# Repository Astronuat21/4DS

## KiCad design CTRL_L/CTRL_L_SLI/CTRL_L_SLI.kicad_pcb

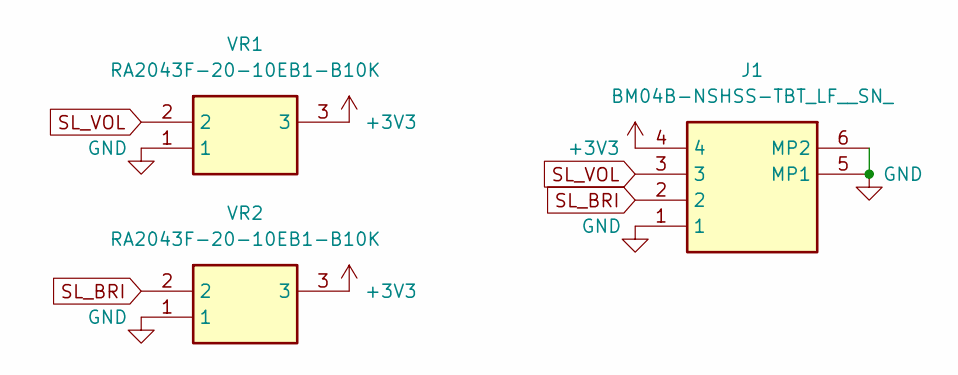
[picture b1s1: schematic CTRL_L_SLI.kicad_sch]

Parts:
J1: BM04B-NSHSS-TBT_LF__SN_; BM04BNSHSSTBTLFSN; Mouser Part Number 306-4BNSHSSTBTL
VR1, VR2: RA2043F-20-10EB1-B10K; RA2043F2010EB1B10K; Mouser Part Number 312-219BF-10K

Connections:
+3V3: J1.4, VR1.3, VR2.3
GND: J1.1, J1.5 (MP1), J1.6 (MP2), VR1.1, VR2.1
SL_BRI: J1.2, VR2.2
SL_VOL: J1.3, VR1.2

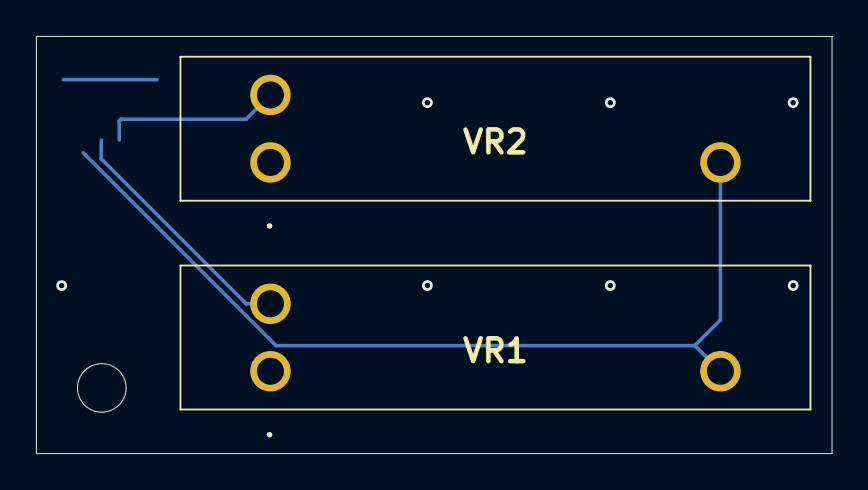
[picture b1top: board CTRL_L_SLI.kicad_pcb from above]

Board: 2 copper layers, 44.2 x 23.2 mm, 3 parts (1 on the bottom side), 4 nets.

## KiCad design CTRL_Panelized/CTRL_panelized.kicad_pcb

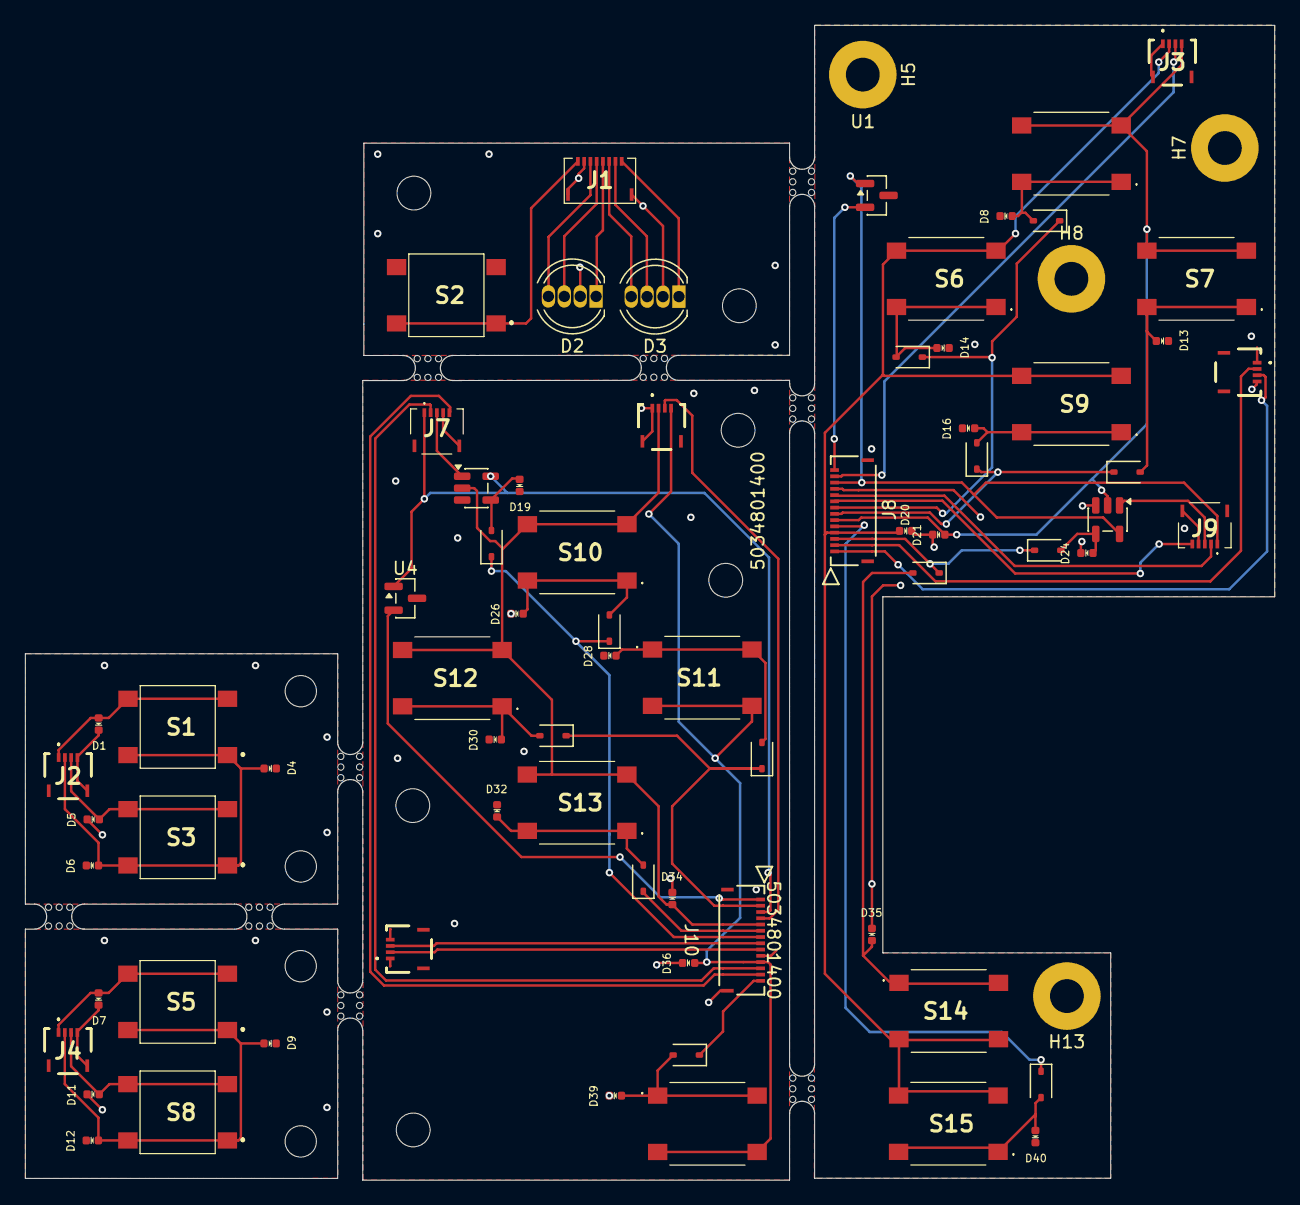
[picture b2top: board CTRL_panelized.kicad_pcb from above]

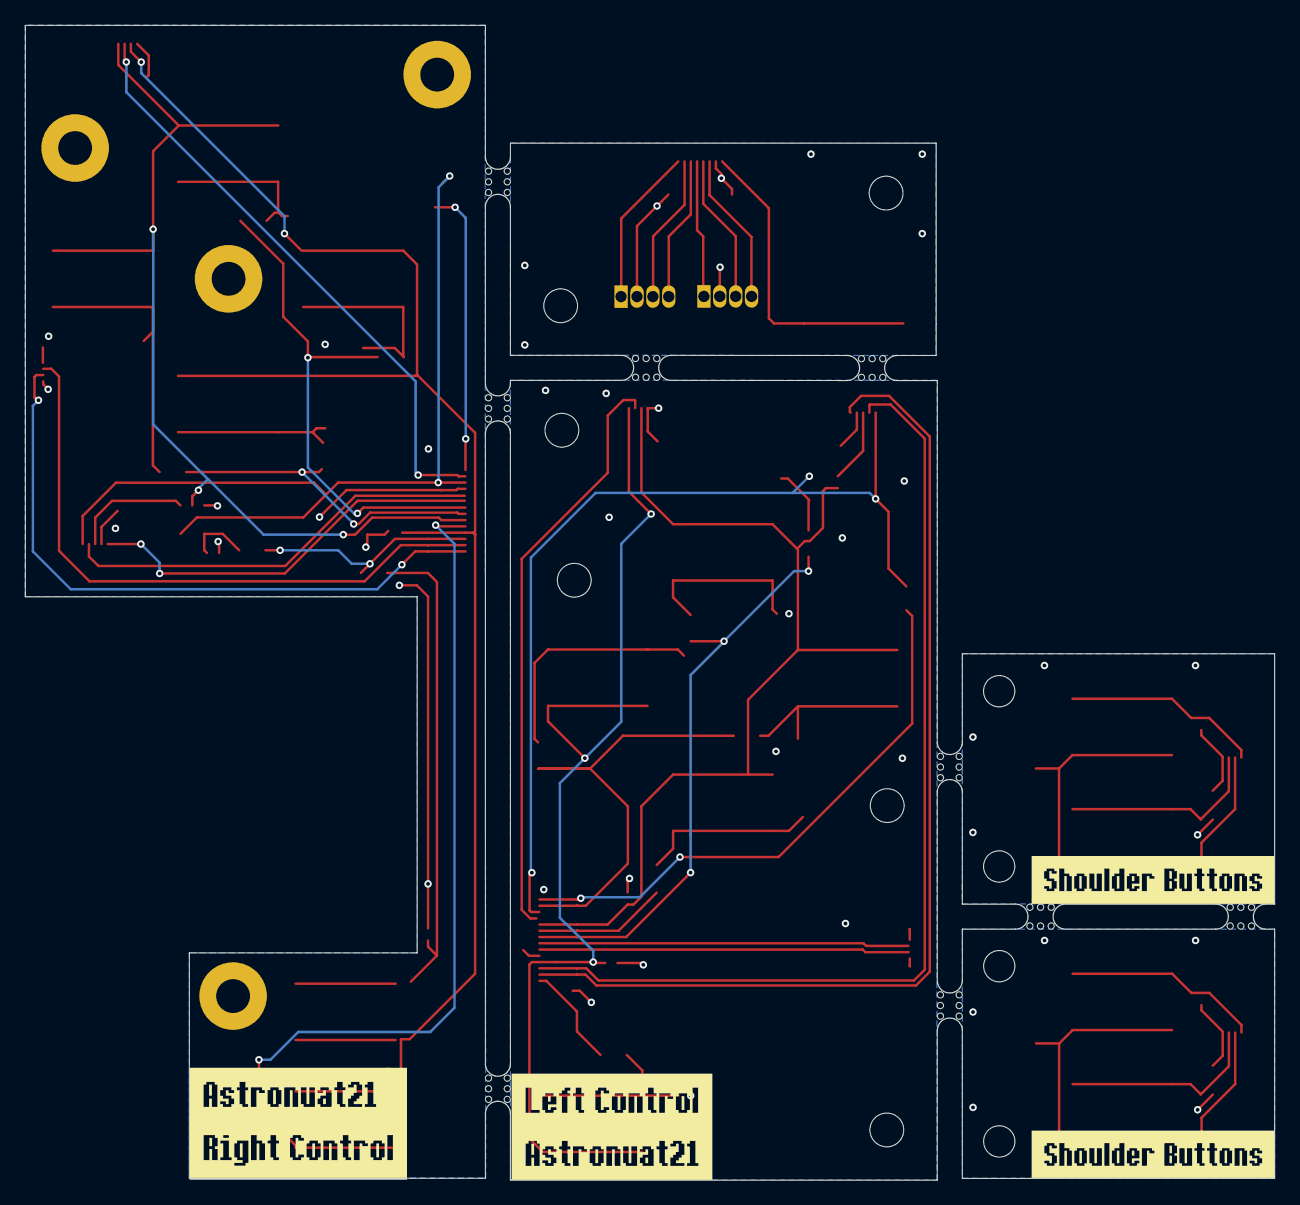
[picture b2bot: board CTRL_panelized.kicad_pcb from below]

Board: 2 copper layers, 99.8 x 92.2 mm, 91 parts (6 on the bottom side), 36 nets.

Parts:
D1, D4, D5, D6, D7, D8, D9, D11, D12, D13, D14, D16, D19, D20, D21, D24, D26, D28, D30, D32, D34, D35, D36, D39, D40: ESD5V0B03; D_0402_1005Metric
D2, D3: LED_RKGB; LED_D5.0mm-4_RGB
D10, D15, D17, D18, D22, D23, D25, D27, D29, D31, D33, D37, D38: 1N4148WS; D_SOD-323
H1, H3, H10, H11, H12, H14: MountingHole; MountingHole_2.7mm_M2.5
H2, H4, H6, H9: MountingHole; MountingHole_2.5mm
H5, H7, H8, H13: MountingHole_Pad; MountingHole_2.7mm_M2.5_Pad
J1: 503480-0800; 5034800800
J2, J3, J4, J5, J6, J11: 503480-0440; 5034800440
J7, J9: 503480-0540; 5034800540
J8, J10: 5034801400
S1, S2, S3, S5, S8: B3S-1002; B3S1002
S4, S6, S7, S9, S10, S11, S12, S13, S14, S15, S16: B3S-1000; B3S1000
U1, U4: DRV5033FAxDBZ; SOT-23
U2, U3: 74LVC1G08; SOT-23-5
kibuzzard-1, kibuzzard-2: G***; kibuzzard-6A70E37C
kibuzzard-3, kibuzzard-6: G***; kibuzzard-6A187131
kibuzzard-4: G***; kibuzzard-6A186FEC
kibuzzard-5: G***; kibuzzard-6A19F3B7

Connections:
+3V3: J7.1, J8.12, J9.1, J10.3, U1.1 (VCC), U2.5 (VCC), U3.5 (VCC), U4.1 (VCC)
/ADC_X: J7.5, J8.9, J9.5, J10.13
/ADC_Y: J7.2, J8.10, J9.2, J10.12
/SW: J7.3, J9.3, U2.1, U3.1
Col1: D34.2 (A2), J6.2, J10.5, S10.3 (NO_1), S10.4 (NO_2), S12.3 (NO_1), S12.4 (NO_2), S13.3 (NO_1), S13.4 (NO_2), U2.2
Col2: D36.2 (A2), J6.4, J10.11, S11.3 (NO_1), S11.4 (NO_2), S16.3 (NO_1), S16.4 (NO_2)
Col3: D20.2 (A2), J3.2, J8.4, S6.3 (NO_1), S6.4 (NO_2), S9.3 (NO_1), S9.4 (NO_2), S14.3 (NO_1), S14.4 (NO_2), S15.3 (NO_1), S15.4 (NO_2)
Col4: D21.2 (A2), J3.4, J8.6, S4.3 (NO_1), S4.4 (NO_2), S7.3 (NO_1), S7.4 (NO_2), U3.2
ColA: D5.2 (A2), D11.2 (A2), J2.3, J4.3, S3.3 (NO_1), S3.4 (NO_2), S8.3 (NO_1), S8.4 (NO_2)
ColB: D1.2 (A2), D7.2 (A2), J2.1, J4.1, S1.3 (NO_1), S1.4 (NO_2), S5.3 (NO_1), S5.4 (NO_2)
GND: D1.1 (A1), D2.2 (K), D3.2 (K), D4.1 (A1), D5.1 (A1), D6.1 (A1), D7.1 (A1), D8.1 (A1), D9.1 (A1), D11.1 (A1), D12.1 (A1), D13.1 (A1), D14.1 (A1), D16.1 (A1), D19.1 (A1), D20.1 (A1), D21.1 (A1), D24.1 (A1), D26.1 (A1), D28.1 (A1), D30.1 (A1), D32.1 (A1), D34.1 (A1), D35.1 (A1), D36.1 (A1), D39.1 (A1), D40.1 (A1), H5.1 (1_1), H7.1 (1_1), H8.1 (1_1), H13.1 (1_1), J1.2, J1.9, J1.10, J2.4, J2.MP1, J2.MP2, J3.1, J3.MP1, J3.MP2, J4.4, J4.MP1, J4.MP2, J5.1, J5.4, J5.MP1, J5.MP2, J6.1, J6.MP1, J6.MP2, J7.4, J7.MP1, J7.MP2, J8.11, J8.P1, J8.P2, J9.4, J9.MP1, J9.MP2, J10.10, J10.P1, J10.P2, J11.1, J11.4, J11.MP1, J11.MP2, S2.3 (NO_1), S2.4 (NO_2), U1.3 (GND), U2.3 (GND), U3.3 (GND), U4.3 (GND)
HALL: J8.14, J10.1, U1.2 (OUT), U4.2 (OUT)
unnamed: D8.2 (A2), D10.2 (A), S4.1 (COM_1), S4.2 (COM_2)
unnamed: D14.2 (A2), D15.2 (A), S6.1 (COM_1), S6.2 (COM_2)
unnamed: D2.4 (BA), J1.3
unnamed: D2.3 (GA), J1.4
unnamed: D2.1 (RA), J1.5
unnamed: D3.4 (BA), J1.6
unnamed: D3.3 (GA), J1.7
unnamed: D3.1 (RA), J1.8
unnamed: D4.2 (A2), D6.2 (A2), D9.2 (A2), D12.2 (A2), D26.2 (A2), D27.2 (A), J2.2, J4.2, S1.1 (COM_1), S1.2 (COM_2), S3.1 (COM_1), S3.2 (COM_2), S5.1 (COM_1), S5.2 (COM_2), S8.1 (COM_1), S8.2 (COM_2), S10.1 (COM_1), S10.2 (COM_2)
unnamed: D25.2 (A), D29.2 (A), D30.2 (A2), D35.2 (A2), S12.1 (COM_1), S12.2 (COM_2), S14.1 (COM_1), S14.2 (COM_2)
unnamed: D28.2 (A2), D31.2 (A), D38.2 (A), D40.2 (A2), S11.1 (COM_1), S11.2 (COM_2), S15.1 (COM_1), S15.2 (COM_2)
unnamed: D16.2 (A2), D17.2 (A), D32.2 (A2), D33.2 (A), S9.1 (COM_1), S9.2 (COM_2), S13.1 (COM_1), S13.2 (COM_2)
unnamed: D13.2 (A2), D18.2 (A), D37.2 (A), D39.2 (A2), S7.1 (COM_1), S7.2 (COM_2), S16.1 (COM_1), S16.2 (COM_2)
unnamed: D19.2 (A2), D22.2 (A), U2.4
unnamed: D23.2 (A), D24.2 (A2), U3.4
unnamed: J1.1, S2.1 (COM_1), S2.2 (COM_2)
Row1: J3.3, J6.3, J8.13, J10.4
Row2: D10.1 (K), D15.1 (K), D22.1 (K), D27.1 (K), J8.8, J10.7
Row3: D17.1 (K), D18.1 (K), D29.1 (K), D31.1 (K), J8.7, J10.2
Row4: D23.1 (K), D25.1 (K), D33.1 (K), J8.3, J10.6
Row5: D37.1 (K), D38.1 (K), J8.5, J10.14
SL_BRI: J5.3, J8.1
SL_VIN: J5.2, J8.2, J10.9, J11.2
SL_VOL: J10.8, J11.3

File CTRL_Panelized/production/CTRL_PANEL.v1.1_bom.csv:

Designator,Footprint,Quantity,Value,LCSC Part #
"D1, D11, D12, D13, D14, D16, D19, D20, D21, D24, D26, D28, D30, D32, D34, D35, D36, D39, D4, D40, D5, D6, D7, D8, D9",0402,25,ESD5V0B03,C521894
"D10, D15, D17, D18, D22, D23, D25, D27, D29, D31, D33, D37, D38",D_SOD-323,13,1N4148WS,C917117
"D2, D3",LED_D5.0mm-4_RGB,2,LED_RKGB,C2837020
J1,5034800800,1,503480-0800,C596711
"J10, J8",5034801400,2,5034801400,C505360
"J11, J5",AYF530365T,2,AYF530365TA,C5571510
"J2, J3, J4, J6",5034800440,4,503480-0440,C3170007
"J7, J9",5034800540,2,503480-0540,C5527934
"S1, S2, S3, S5, S8",B3S1002,5,B3S-1002,C2733654
"S10, S11, S12, S13, S14, S15, S16, S4, S6, S7, S9",B3S1000,11,B3S-1000,C2733655
"U1, U4",SOT-23,2,DRV5033FAxDBZ,C2869057
"U2, U3",SOT-23-5,2,74LVC1G08,C53185136

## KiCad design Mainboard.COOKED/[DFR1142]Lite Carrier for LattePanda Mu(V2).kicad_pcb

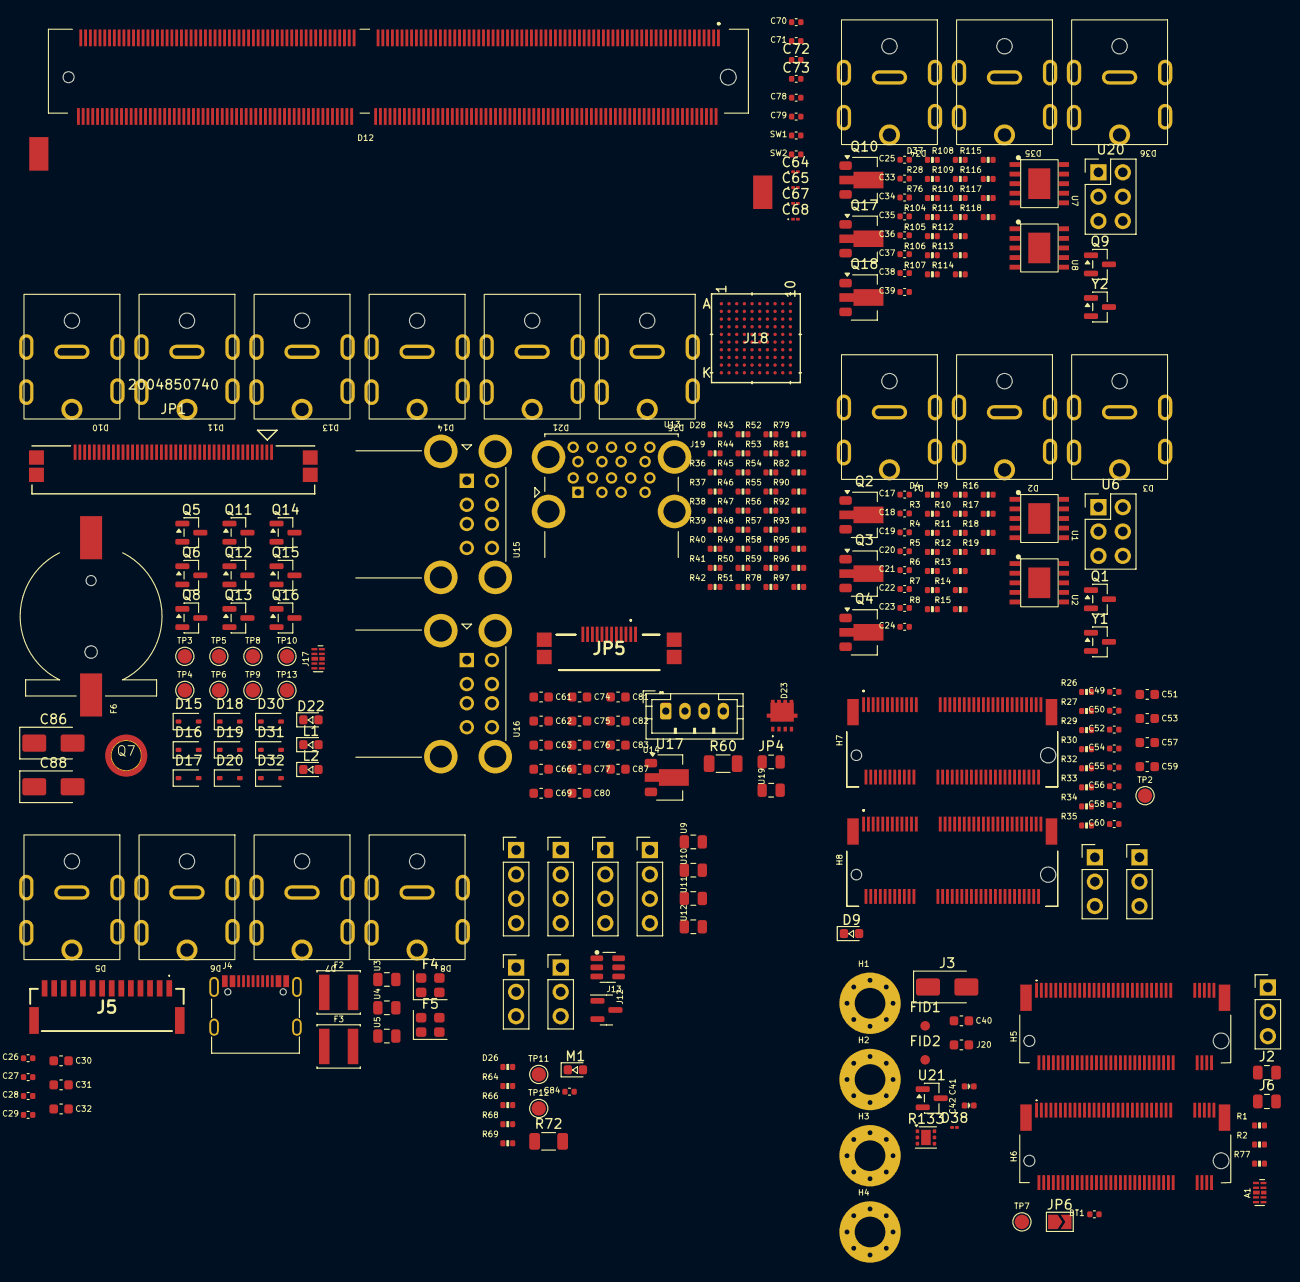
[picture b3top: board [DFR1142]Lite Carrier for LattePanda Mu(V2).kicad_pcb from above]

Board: 4 copper layers, 283 parts (0 on the bottom side), 110 nets, no tracks yet.

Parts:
A1: ULC0524P; Diodes_UDFN-10_1.0x2.5mm_P0.5mm
BT1: 220nF/16V; C_0402_1005Metric
C17, C18, C19, C20, C21, C22, C23, C24, C25, C26, C27, C28, C29, C33, C34, C35, C36, C37, C38, C39, C52, C54, C58, C60, C70, C71, C78, C79, C84: 10uF/10V; C_0402_1005Metric
C30, C31, C32, C74, C75, C76, C77, C80, C81, C82, C83: 4.7uF; C_0603_1608Metric
C40: 220nF; C_0603_1608Metric
C41: 0402ESDA-05N; D_0402_1005Metric
C42: PESD24VS1UL-N; D_0402_1005Metric
C49, C50, C55, C56: 1uF/16V; C_0402_1005Metric
C51, C53, C57, C59, C87: 22uF/10V; C_0603_1608Metric
C61, C62, C63, C66, C69: 1uF; C_0603_1608Metric
C64, C65, C67, C68: D; D_01005_0402Metric
C72, C73: 12pF/50V; C_0402_1005Metric
C86, C88: SMAJ26CA; D_SMA
D1, D2, D3, D5, D6, D7, D8, D10, D11, D13, D14, D21, D25, D34, D35, D36: Barrel_Jack_Switch; DC_Jack_DC007B_30V_10A
D4, D26, D28, D37: 1K/1%; R_0402_1005Metric
D9, D22: LED_G; LED_0603_1608Metric
D12: LattePanda_Module_Gen1; DDR4_SODIMM_260P_8.0H_STD
D15, D16, D17, D18, D19, D20, D30, D31, D32: 1N5819WS; D_SOD-323
D23: NCE30P28Q; MOSFET_PDFN8_3.3x3.3
D38: 0.57Ohm; L_01005_0402Metric
F2, F3: 2.2uH/4.3A; L_Sunlord_SWPA4020S
F4, F5: SiT8008xx-1x-xxE; Oscillator_SMD_SiT_PQFN-4Pin_2.5x2.0mm
F6: Battery_Cell; Battery_Holder_CR1220_S8411-45R
FID1, FID2: Fiducial; Fiducial_1mm_Mask2mm
H1, H2, H3, H4: MountingHole_Pad; MountingHole_3.2mm_M3_Pad_Via
H5, H6: Bus_M.2_Socket_M; PCIe_M.2_Connectors_P=0.5mm_H=4.2mm_KeyM
H7, H8: Bus_M.2_Socket_E; PCIe_M.2_Connectors_P=0.5mm_H=4.2mm_KeyE
J1, J8, J11, J15, J16: Conn_01x03_Pin; PinHeader_1x03_P2.54mm_Vertical
J2, J6: 22uF/25V; C_0805_2012Metric
J3: SS54; D_SMA
J4: USB_C_Receptacle_USB2.0; USB_C_Receptacle_G-Switch_GT-USB-7010ASV
J5: BM14B-NSHSS-TBT_LF__SN_; BM14BNSHSSTBTLFSN
J7, J9, J10, J14: Conn_01x04_Pin; PinHeader_1x04_P2.54mm_Vertical
J12: TL431DBZ; SOT-23
J13: SY8253ADC; TSOT-23-6
J17: TPAZ1023-04F; Diodes_UDFN-10_1.0x2.5mm_P0.5mm
J18: ADV7613WBBCZ; BC_100_4_ADI
J19: 10K/1%; R_0402_1005Metric
J20: 2.2uF/50V; C_0603_1608Metric
JP1: 2004850740; CON_2004850740
JP4: 6V/2A; Fuse_0805_2012Metric
JP5: 200485-0710; 2004850710
JP6: SolderJumper_2_Open; SolderJumper-2_P1.3mm_Open_TrianglePad1.0x1.5mm
L1, L2: LED_R; LED_0603_1608Metric
M1: LED_G; LED_0603_1608Metric
Q1, Q5, Q6, Q8, Q9, Q11, Q12, Q13, Q14, Q15, Q16: AO3407; SOT-23
Q2, Q3, Q4, Q10, Q17, Q18: HM7533HBPR; SOT-89-3
Q7: MountingHole_Pad; MountingHole_3mm_M2_Pad_TopOnly
R1, R11, R37, R47, R78, R90, R110: 2.2K/1%; R_0402_1005Metric
R2, R34, R35, R36, R38, R40, R49, R58, R79: 1M/1%; R_0402_1005Metric
R3, R5, R15, R18, R19, R28, R30, R39, R52, R53, R66, R104, R114, R117, R118: 21.5K/1%; R_0402_1005Metric
R4, R76, R81: 470R/1%; R_0402_1005Metric
R6, R12, R26, R41, R42, R54, R59, R68, R105, R111: 0R/1%; R_0402_1005Metric
R7, R8, R9, R10, R13, R14, R16, R17, R97, R106, R107, R108, R109, R112, R113, R115, R116: 56K/1%; R_0402_1005Metric
R27, R29, R32, R33, R95, R96: 100K/1%; R_0402_1005Metric
R43: 100R/1%; R_0402_1005Metric
R44, R45, R51, R77, R82: 75K/1%; R_0402_1005Metric
R46, R48, R55, R64, R69, R92, R93: 4.7K/1%; R_0402_1005Metric
R50, R56: 10K/1%; R_0402_1005Metric
R57: 200R/1%; R_0402_1005Metric
R60, R72: BSMD1206C-2100T; R_1206_3216Metric
R133: TPS61165DBV; WSON-6-1EP_2x2mm_P0.65mm_EP1x1.6mm
SW1, SW2: 100nF/16V; C_0402_1005Metric
TP2, TP3, TP4, TP5, TP6, TP7, TP8, TP9, TP10, TP11, TP12, TP13: TestPoint; TestPoint_Pad_D1.5mm
U1, U2, U7, U8: CH224K; ESSOP-10-1EP_3.9x5mm_P1.0mm_EP3.2x2.3
U3, U4, U5, U9, U10, U11, U12, U19: 6V/1A; Fuse_0805_2012Metric
U6, U20: PinHeader_2x03_P2.54mm_Vertical
U13: USB3_A_Stacked; USB3_A_Molex_48406-0001_Horizontal_Stacked
U14: Fan_4pin; JST_PH_B4B-PH-K_1x04_P2.00mm_Vertical
U15, U16: USB_A_Stacked; USB_A_CUI_UJ2-ADH-TH_Horizontal_Stacked
U17: HM7533HBPR; SOT-89-3
U21: 2SK3018; SOT-23
Y1, Y2: 2N7002; SOT-23

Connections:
5V_HDMI_VCC: D4.1 (K), D37.1 (K), R15.1, R18.1, R114.1, R117.1
+1V8: Y1.1 (OE), Y2.1 (OE)
+3V3: C51.2, C52.2, C53.2, C54.2, C57.2, C58.2, C59.2, C60.2, C73.1, C75.2, C77.2, C79.1, C81.2, C83.2, J3.2 (2_2), J13.1, J13.2, J13.3, J13.4, J14.1, J14.2, J14.3, J15.2 (3.3V), J16.2 (3.3V), J20.2, L2.2, Q1.1 (G), Q2.1 (G), Q3.1 (G), Q9.1 (G), Q10.1 (G), Q17.1 (G), R3.1, R4.1, R5.1, R28.1, R30.2, R34.2, R35.1, R50.2, R56.2, R59.2, R64.1, R76.1, R104.1, TP6.1 (1_1)
+3V3_ROM: C88.1, D28.1 (K), R2.2, R52.2, R53.2, R81.1, R82.1, R97.1, TP13.1 (1_1), U17.3 (VOUT)
+5V: C30.2, C31.2, C32.2, C41.2, C72.1, C74.2, C76.2, C78.1, C80.2, C82.2, D4.2 (A), D37.2 (A), F2.1, F3.1, F4.1, F5.1, L1.2, Q16.2 (S), R57.2, TP5.1 (1_1), U21.1 (VIN)
+5V_FAN: C84.1, D26.1 (K), M1.2 (+), Q16.3 (D), R72.1
+12V: C63.2, D15.2 (A), D16.2 (A), D17.2 (A), F6.2, Q7.1 (S_1_1), R38.2, R40.2, R44.2, TP4.1 (1_1)
+12VA: R54.1, TP8.1 (1_1)
+15V: D12.1 (K), D18.2 (A), D19.2 (A), D20.2 (A), J18.A4 (VBUS), J18.A9 (VBUS), J18.B4 (VBUS), J18.B9 (VBUS), R36.1, R37.1, TP3.1 (1_1)
+VBAT: D30.2 (A), D31.2 (A), D32.2 (A), J19.1, J19.2
/Fan_Temp/FAN_1_PWM: A1.2 (FAN_CTL2), R64.2, R69.1, TP12.1 (1_1)
/Fan_Temp/FAN_1_TAC: A1.4 (FAN_TAC2), R66.1, R68.2, TP11.1 (1_1)
/GPIO/I2C2_SCL: J9.1, U11.1
/GPIO/I2C2_SDA: J7.1, U9.1
/GPIO/I2C3_SCL: J9.2, U11.2
/GPIO/I2C3_SDA: J7.2, U9.2
/GPIO/SOC_UART0_RX: J8.1, U10.1
/GPIO/SOC_UART0_TX: J10.1, U12.1
/GPIO/SOC_UART1_RX: J8.2, U10.2
/GPIO/SOC_UART1_TX: J10.2, U12.2
/HDMI-LVDS1/DDC_SCL: D34.2 (A2), Q10.3 (D), R114.2
/HDMI-LVDS1/DDC_SDA: D36.2 (A2), Q17.3 (D), R117.2
/HDMI-LVDS1/HPD: D35.2 (A2), R110.2
/HDMI-LVDS1/TCP_0_DDC_SCL: Q10.2 (S), R104.2
/HDMI-LVDS1/TCP_0_DDC_SDA: Q17.2 (S), R28.2
/HDMI-LVDS1/TCP_0_HPD: Q9.2 (S), R76.2
/HDMI-LVDS1/TMDS_CK+: C38.2, R107.1, U8.4, U8.7 (NC)
/HDMI-LVDS1/TMDS_CK-: C39.2, R106.1, U8.5, U8.6 (NC)
/HDMI-LVDS1/TMDS_D0+: C36.2, R109.1, U8.1, U8.10 (NC)
/HDMI-LVDS1/TMDS_D0-: C37.2, R108.1, U8.2, U8.9 (NC)
/HDMI-LVDS1/TMDS_D1+: C34.2, R113.1, U7.4, U7.7 (NC)
/HDMI-LVDS1/TMDS_D1-: C35.2, R112.1, U7.5, U7.6 (NC)
/HDMI-LVDS1/TMDS_D2+: C25.2, R116.1, U7.1, U7.10 (NC)
/HDMI-LVDS1/TMDS_D2-: C33.2, R115.1, U7.2, U7.9 (NC)
/HDMI-LVDS/DDC_SCL: D1.2 (A2), Q2.3 (D), R15.2
/HDMI-LVDS/DDC_SDA: D3.2 (A2), Q3.3 (D), R18.2
/HDMI-LVDS/HPD: D2.2 (A2), R11.2
/HDMI-LVDS/TCP_0_DDC_SCL: Q2.2 (S), R5.2
/HDMI-LVDS/TCP_0_DDC_SDA: Q3.2 (S), R3.2
/HDMI-LVDS/TCP_0_HPD: Q1.2 (S), R4.2
/HDMI-LVDS/TMDS_CK+: C23.2, R8.1, U2.4, U2.7 (NC)
/HDMI-LVDS/TMDS_CK-: C24.2, R7.1, U2.5, U2.6 (NC)
/HDMI-LVDS/TMDS_D0+: C21.2, R10.1, U2.1, U2.10 (NC)
/HDMI-LVDS/TMDS_D0-: C22.2, R9.1, U2.2, U2.9 (NC)
/HDMI-LVDS/TMDS_D1+: C19.2, R14.1, U1.4, U1.7 (NC)
/HDMI-LVDS/TMDS_D1-: C20.2, R13.1, U1.5, U1.6 (NC)
/HDMI-LVDS/TMDS_D2+: C17.2, R17.1, U1.1, U1.10 (NC)
/HDMI-LVDS/TMDS_D2-: C18.2, R16.1, U1.2, U1.9 (NC)
/LattePanda Module/SUSCLK_WIFI: R29.2, R33.2
/LattePanda Module/~PWR_SW: A1.1 (~PWR_SW), JP5.1 (A), R48.2, R92.1
/LattePanda Module/~RST_SW: A1.3 (~RST_SW), R55.2
/PSU/CC1: D13.2 (A2), J18.A5 (CC1)
/PSU/CC2: D14.2 (A2), J18.B5 (CC2)
/PSU/POWER_SW: C66.1, D21.2 (A2), R48.1, R50.1, SW1.1
/PSU/PWR_C_D+: D11.2 (A2), J18.A6 (D+), J18.B6 (D+), U14.4 (DP)
/PSU/PWR_C_D-: D10.2 (A2), J18.A7 (D-), J18.B7 (D-)
/PSU/PWR_EN: Q15.1 (G), R46.2, R51.2, TP9.1 (1_1), U15.4 (EN), U16.4 (EN)
/PSU/RESET_SW: C69.1, D25.2 (A2), R55.1, R56.1, SW2.1
/PSU/UPS_STATE_LP: R93.1, U19.1
/PSU/UPS_SW_LP: R92.2, U19.2
/PSU/~SLP_S4_N: A1.7 (SLP_S4_N), JP1.3 (B), R78.1, R93.2
/USB2.0&USB3.0/CON_USB1_D_N: J5.2 (D1-), U4.2
/USB2.0&USB3.0/CON_USB1_D_P: J5.3 (D1+), U4.1
/USB2.0&USB3.0/CON_USB4_SSTX_N: C28.2, U3.1
/USB2.0&USB3.0/CON_USB4_SSTX_P: C29.2, U3.2
/~PWR_LED/~PSON: A1.5 (~PWR_LED/~PSON), JP1.1 (A), Q6.1 (G), R19.1, R47.1
GND: BT1.2 (-), C30.1, C31.1, C32.1, C40.1, C41.1, C42.1, C51.1, C52.1, C53.1, C54.1, C57.1, C58.1, C59.1, C60.1, C61.2, C62.2, C64.1, C65.1, C66.2, C67.1, C68.1, C69.2, C74.1, C75.1, C76.1, C77.1, C78.2, C79.2, C80.1, C81.1, C82.1, C83.1, C84.2, C86.2, C87.2, C88.2, D1.1 (A1), D2.1 (A1), D3.1 (A1), D5.1 (A1), D6.1 (A1), D7.1 (A1), D8.1 (A1), D10.1 (A1), D11.1 (A1), D12.2 (A), D13.1 (A1), D14.1 (A1), D21.1 (A1), D23.1 (K), D25.1 (A1), D34.1 (A1), D35.1 (A1), D36.1 (A1), H1.1 (1_1), H2.1 (1_1), H3.1 (1_1), H4.1 (1_1), H5.1 (1_1), H6.1 (1_1), H7.1 (1_1), H8.1 (1_1), J1.3, J5.4 (GND1), J5.8 (GND2), J5.9 (Shield), J11.1, J11.2, J11.3, J12.1, J12.2, J12.3, J15.1 (GND), J15.3 (GND), J16.1 (GND), J17.2, J17.3, J18.A1 (GND), J18.B1 (GND), J20.1, JP4.1, JP4.2, JP6.1 (A), M1.1 (-), Q4.2 (S), Q6.2 (S), Q8.2 (S), Q12.2 (S), Q13.2 (S), Q14.2 (S), Q15.2 (S), Q18.2 (S), R6.2, R12.2, R27.2, R32.2, R39.1, R42.1, R43.2, R49.1, R51.1, R58.1, R60.1, R66.2, R77.2, R79.1, R97.2, R105.2, R111.2, SW1.2, SW2.2, U1.3 (VSS), U1.8 (VSS), U2.3 (VSS), U2.8 (VSS), U7.3 (VSS), U7.8 (VSS), U8.3 (VSS), U8.8 (VSS), U13.3 (A), U15.2 (GND), U16.2 (GND), U17.1 (GND), Y1.2 (GND), Y2.2 (GND)
LED+: C40.2, D38.1 (K)
unnamed: A1.10 (SIO_UART_TX), J1.1
unnamed: JP6.2 (B), R2.1, TP7.1 (1_1)
unnamed: BT1.1 (+), R1.2
unnamed: D9.2 (A), R30.1
unnamed: D22.2 (A), R52.1
unnamed: D22.1 (K), Q8.3 (D), R90.1
unnamed: D23.2 (A), R54.2
unnamed: D26.2 (A), R68.1, R72.2
unnamed: C87.1, D28.2 (A), Q13.1 (G), R81.2
unnamed: D38.2 (A), U21.3 (SW)
unnamed: F6.1, J17.1
unnamed: F2.2, J5.1 (VBUS1)
unnamed: F3.2, J5.5 (VBUS2)
unnamed: R26.2, R27.1
unnamed: JP1.2 (C), R46.1
unnamed: JP5.2 (C), Q12.3 (D)
unnamed: Q1.3 (D), R6.1, R11.1
unnamed: Q4.3 (D), R7.2, R8.2, R9.2, R10.2, R12.1, R13.2, R14.2, R16.2, R17.2
unnamed: Q4.1 (G), R19.2
unnamed: Q5.3 (D), R45.1
unnamed: C62.1, Q5.1 (G), R41.1, R42.2
unnamed: Q5.2 (S), Q6.3 (D)
unnamed: C63.1, R44.1, R45.2
unnamed: Q8.1 (G), R47.2, R49.2
unnamed: Q9.3 (D), R105.1, R110.1
unnamed: Q11.1 (G), R78.2, R79.2
unnamed: Q11.2 (S), Q14.3 (D)
unnamed: Q12.1 (G), Q13.3 (D), R82.2
unnamed: Q14.1 (G), R90.2
unnamed: Q15.3 (D), Q16.1 (G)
unnamed: Q18.3 (D), R106.2, R107.2, R108.2, R109.2, R111.1, R112.2, R113.2, R115.2, R116.2
unnamed: Q18.1 (G), R118.2
unnamed: R40.1, R41.2, U13.1 (K)
unnamed: R38.1, R39.2, U13.2 (REF)
unnamed: C61.1, R37.2, U14.1 (VDD)
unnamed: C70.2, U15.1 (BOOST)
unnamed: C72.2, R57.1, R58.2, U15.3 (FB)
unnamed: C70.1, L1.1, U15.6 (SW)
unnamed: C71.2, U16.1 (BOOST)
unnamed: C73.2, R59.1, R60.2, U16.3 (FB)
unnamed: C71.1, L2.1, U16.6 (SW)
VDC: C64.2, C65.2, C67.2, C68.2, C86.1, D15.1 (K), D16.1 (K), D17.1 (K), D18.1 (K), D19.1 (K), D20.1 (K), D30.1 (K), D31.1 (K), D32.1 (K), TP10.1 (1_1), U15.5 (VIN), U16.5 (VIN), U17.2 (VIN)

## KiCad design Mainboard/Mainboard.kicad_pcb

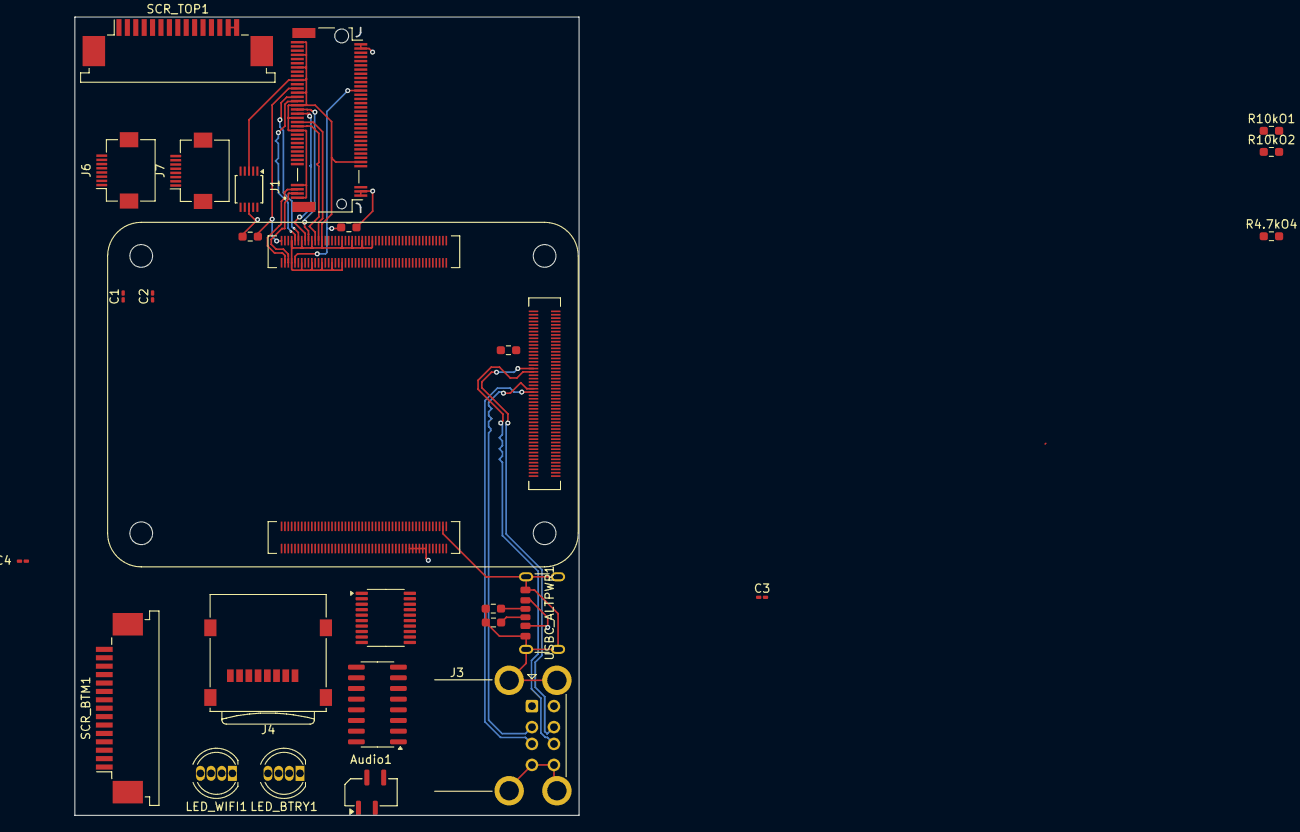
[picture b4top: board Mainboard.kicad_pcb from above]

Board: 4 copper layers, 60.0 x 95.0 mm, 27 parts (0 on the bottom side), 72 nets.

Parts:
Audio1: Conn_01x04_Socket; TE_84982-4_2Rows-04Pins-P1.0mm_Vertical
C1, C2, C3, C4: C_Small_US; C_0201_0603Metric_Pad0.64x0.40mm_HandSolder
J1: Bus_M.2_Socket_E; TE_2199230-8
J3: USB_A_Stacked; USB_A_CUI_UJ2-ADH-TH_Horizontal_Stacked
J4: Micro_SD_Card; microSD_HC_Wuerth_693072010801
J6, J7: Conn_01x09_Pin; Hirose_FH12-8S-0.5SH_1x08-1MP_P0.50mm_Horizontal
LED_BTRY1: LED_BGKR; LED_D5.0mm-4_RGB
LED_WIFI1: LED_BGKR; LED_D5.0mm-4_RGB
R4.7kO1, R4.7kO2, R4.7kO3, R4.7kO4, R10kO1, R10kO2: R; R_0603_1608Metric_Pad0.98x0.95mm_HandSolder
R~{5.1kO}1, R~{5.1kO}2: R; R_0603_1608Metric_Pad0.98x0.95mm_HandSolder
SCR_BTM1: Conn_01x15_Socket; TE_1-84953-5_1x15-1MP_P1.0mm_Horizontal
SCR_TOP1: Conn_01x15_Socket; TE_1-84953-5_1x15-1MP_P1.0mm_Horizontal
U1: Hirose DF40C-100DS-0.4V; Radxa_CM5
U2: ADS1115IDGS; TSSOP-10_3x3mm_P0.5mm
U3: PCM5102; TSSOP-20_4.4x6.5mm_P0.65mm
U4: PAM8403D; SOP-16_3.9x9.9mm_P1.27mm
USBC_ALTPWR1: USB_C_Receptacle_PowerOnly_6P; USB_C_Receptacle_GCT_USB4125-xx-x-0190_6P_TopMnt_Horizontal

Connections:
+5V: C1.1, C2.1, J3.1 (VBUS1), J3.5 (VBUS2), U1.77 (+5v_(Input)), U1.79 (+5v_(Input)), U1.81 (+5v_(Input)), U1.83 (+5v_(Input)), U1.85 (+5v_(Input)), U1.87 (+5v_(Input)), USBC_ALTPWR1.A9 (VBUS), USBC_ALTPWR1.B9 (VBUS)
/3V3: C3.2, J1.2 (3.3V), J1.4 (3.3V), J1.72 (3.3V), J1.74 (3.3V), J4.4 (VDD), J6.1, J7.1, R4.7kO1.2, R4.7kO2.2, R4.7kO3.1, R4.7kO4.1, R10kO1.1, R10kO2.2, SCR_BTM1.14, SCR_BTM1.15, SCR_TOP1.14, SCR_TOP1.15, U1.86 (+3.3v_(Output)), U2.8 (VDD), U3.20 (DVDD), U4.4 (PVDD), U4.13 (PVDD)
/PER+: J1.41 (PERp0), U1.116 (PCIe_RX_P)
/PER-: J1.43 (PERn0), U1.118 (PCIe_RX_N)
/PET+: J1.35 (PETp0), U1.122 (PCIe_TX_P)
/PET-: J1.37 (PETn0), U1.124 (PCIe_TX_N)
/RFCLK+: J1.47 (REFCLKp0), U1.110 (PCIe_CLK_P)
/RFCLK-: J1.49 (REFCLKn0), U1.112 (PCIe_CLK_N)
/USB1_D+: J3.3 (D1+), U1.251 (USB3_HOST1_SSTXP)
/USB1_D-: J3.2 (D1-), U1.253 (USB3_HOST1_SSTXN)
/USB2_D+: J3.7 (D2+), U1.263 (USB2_HOST2_DP)
/USB2_D-: J3.6 (D2-), U1.265 (USB2_HOST2_DM)
/Wifi+: J1.3 (USB_D+), U1.105 (USB2_P)
/Wifi-: J1.5 (USB_D-), U1.103 (USB2_N)
GND: C1.2, C2.2, C3.1, J1.1 (GND), J1.7 (GND), J1.18 (GND), J1.33 (GND), J1.39 (GND), J1.45 (GND), J1.51 (GND), J1.57 (GND), J1.63 (GND), J1.69 (GND), J1.75 (GND), J3.4 (GND1), J3.8 (GND2), J3.SH (Shield), J4.6 (VSS), J4.9 (SHIELD), LED_BTRY1.3 (K), LED_WIFI1.3 (K), R~{5.1kO}1.1, R~{5.1kO}2.1, SCR_BTM1.1, SCR_BTM1.4, SCR_BTM1.7, SCR_BTM1.10, SCR_BTM1.13, SCR_TOP1.1, SCR_TOP1.4, SCR_TOP1.7, SCR_TOP1.10, SCR_TOP1.13, U1.1 (GND), U1.2 (GND), U1.7 (GND), U1.8 (GND), U1.13 (GND), U1.14 (GND), U1.22 (GND), U1.23 (GND), U1.32 (GND), U1.33 (GND), U1.42 (GND), U1.43 (GND), U1.52 (GND), U1.59 (GND), U1.60 (GND), U1.65 (GND), U1.66 (GND), U1.71 (GND), U1.74 (GND), U1.98 (GND), U1.107 (GND), U1.108 (GND), U1.113 (GND), U1.114 (GND), U1.119 (GND), U1.120 (GND), U1.125 (GND), U1.126 (GND), U1.131 (GND), U1.137 (GND), U1.138 (GND), U1.144 (GND), U1.150 (GND), U1.155 (GND), U1.156 (GND), U1.161 (GND), U1.162 (GND), U1.167 (GND), U1.168 (GND), U1.173 (GND), U1.174 (GND), U1.179 (GND), U1.180 (GND), U1.185 (GND), U1.186 (GND), U1.191 (GND), U1.192 (GND), U1.197 (GND), U1.198 (GND), U1.201 (GND), U1.202 (GND), U1.207 (GND), U1.213 (GND), U1.219 (GND), U1.222 (GND), U1.225 (GND), U1.231 (GND), U1.232 (GND), U1.237 (GND), U1.243 (GND), U1.248 (GND), U1.249 (GND), U1.255 (GND), U1.256 (GND), U1.261 (GND), U1.262 (GND), U1.267 (GND), U1.268 (GND), U1.272 (GND), U1.273 (GND), U1.276 (GND), U1.299 (GND), U1.300 (GND), U2.3 (GND), U3.11 (FLT), U3.19 (DGND), U4.2 (PGND), U4.15 (PGND), USBC_ALTPWR1.A12 (GND), USBC_ALTPWR1.B12 (GND), USBC_ALTPWR1.S1 (SHIELD)
unnamed: Audio1.1, U4.1 (LOUT+)
unnamed: Audio1.2, U4.3 (LOUT-)
unnamed: Audio1.3, U4.14 (ROUT-)
unnamed: Audio1.4, U4.16 (ROUT+)
unnamed: J1.53 (~CLKREQ0), R4.7kO1.1, U1.102 (PCIe_CLK_nREQ)
unnamed: J1.6 (~LED_1), LED_WIFI1.1 (BA), LED_WIFI1.2 (GA)
unnamed: J1.52 (~PERST0), R4.7kO2.1, U1.109 (PCIe_nRST)
unnamed: J4.5 (CLK), U1.57 (SD_CLK)
unnamed: J4.3 (CMD), U1.62 (SD_CMD)
unnamed: J4.7 (DAT0), U1.63 (SD_DAT0)
unnamed: J4.8 (DAT1), U1.67 (SD_DAT1)
unnamed: J4.1 (DAT2), U1.69 (SD_DAT2)
unnamed: J4.2 (DAT3/CD), U1.61 (SD_DAT3)
unnamed: J6.2, U2.4 (AIN0)
unnamed: J6.3, U2.5 (AIN1)
unnamed: J6.4, U1.38 (GPIO11)
unnamed: J6.5, U1.24 (GPIO26)
unnamed: J6.6, U1.26 (GPIO19)
unnamed: J6.7, U1.28 (GPIO13)
unnamed: J6.8, U1.30 (GPIO6)
unnamed: J7.2, U2.6 (AIN2)
unnamed: J7.3, U2.7 (AIN3)
unnamed: J7.4, U1.40 (GPIO9)
unnamed: J7.5, U1.44 (GPIO10)
unnamed: J7.6, U1.54 (GPIO4)
unnamed: J7.7, U1.56 (GPIO3)
unnamed: J7.8, U1.58 (GPIO2)
unnamed: LED_BTRY1.1 (BA), U1.55 (GPIO14)
unnamed: LED_BTRY1.2 (GA), U1.51 (GPIO15)
unnamed: LED_BTRY1.4 (RA), U1.49 (GPIO18)
unnamed: SCR_BTM1.2, U1.175 (DSI1_D0_N)
unnamed: SCR_BTM1.3, U1.177 (DSI1_D0_P)
unnamed: SCR_BTM1.5, U1.187 (DSI1_C_N)
unnamed: SCR_BTM1.6, U1.189 (DSI1_C_P)
unnamed: SCR_BTM1.8, U1.181 (DSI1_D1_N)
unnamed: SCR_BTM1.9, U1.183 (DSI1_D1_P)
unnamed: R4.7kO3.2, SCR_BTM1.11, SCR_TOP1.11, U1.269 (I2C_SDA_3V3)
unnamed: R4.7kO4.2, SCR_BTM1.12, SCR_TOP1.12, U1.271 (I2C_SCL_3V3)
unnamed: SCR_TOP1.2, U1.163 (DSI0_D1_N)
unnamed: SCR_TOP1.3, U1.165 (DSI0_D1_P)
unnamed: SCR_TOP1.5, U1.169 (DSI0_C_N)
unnamed: SCR_TOP1.6, U1.171 (DSI0_C_P)
unnamed: SCR_TOP1.8, U1.159 (DSI0_D0_P)
unnamed: SCR_TOP1.9, U1.157 (DSI0_D0_N)
unnamed: U1.34 (GPIO5), U3.14 (DIN)
unnamed: U1.50 (GPIO17), U3.12 (SCK)
unnamed: U1.46 (GPIO22), U3.13 (BCK)
unnamed: U1.48 (GPIO27), U3.15 (LRCK)
unnamed: R10kO2.1, U1.80 (SCL0), U2.10 (SCL)
unnamed: R10kO1.2, U1.82 (SDA0), U2.9 (SDA)
unnamed: C4.1, U3.9 (AGND), U4.11 (GND)
unnamed: U3.8 (AVDD), U4.6 (VDD)
unnamed: U3.6 (OUTL), U4.7 (INL)
unnamed: U3.7 (OUTR), U4.10 (INR)
unnamed: C4.2, U4.8 (VREF)
unnamed: R~{5.1kO}1.2, USBC_ALTPWR1.A5 (CC1)
unnamed: R~{5.1kO}2.2, USBC_ALTPWR1.B5 (CC2)
